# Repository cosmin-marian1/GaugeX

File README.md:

# GaugeX

A compact three-gauge automotive pod: three GC9A01 1.28" round SPI displays in
fused tubes, driven by an STM32G474, on one 3.3 V rail from switched ignition,
with a listen-only CAN interface.

| Part | State | Entry point |
|---|---|---|
| Enclosure (OpenSCAD) | done, STLs exported | [`3d-model/README.md`](3d-model/README.md) |
| Schematic | ERC 0 violations | [`pcb/DESIGN.md`](pcb/DESIGN.md) §5.3 |
| PCB | routed, planes filled, DRC 0 errors | [`pcb/README.md`](pcb/README.md) |
| BOM | generated from the schematic fields | [`pcb/BOM.md`](pcb/BOM.md) |
| Buck / front-end model | proxy model, timings checked | [`pcb/sim/README.md`](pcb/sim/README.md) |
| Firmware | not started | [`firmware/README.md`](firmware/README.md) |

Everything still open — including the items that block fabrication — is in
[`pcb/OPEN-ITEMS.md`](pcb/OPEN-ITEMS.md).

## Repository map

| Path | Contents |
|---|---|
| `3d-model/` | parametric OpenSCAD source, checkers, STLs, renders |
| `pcb/` | KiCad project (`pcb/GaugeX/`), design/BOM/status docs, simulation |
| `docs/datasheets/` | datasheet PDFs + index with verified page citations |
| `docs/archive/` | superseded documents, kept for traceability only |
| `firmware/` | STM32 firmware (placeholder) |

Each design value has one owner:

| Values | Owner |
|---|---|
| Electronics (power, buck, pins, interfaces, heights) | `pcb/DESIGN.md` |
| Board mechanics, stackup, routing, rules, DRC | `pcb/README.md` |
| Parts, MPN, LCSC | `pcb/BOM.md` |
| Enclosure dimensions and tolerances | `3d-model/README.md` |
| Open checks | `pcb/OPEN-ITEMS.md` |

## Build and verify

Enclosure (exports both STLs, checks the envelope, renders previews):

```bash
cd 3d-model/src && ./export_final.sh
```

Schematic and board checks:

```bash
kicad-cli sch erc pcb/GaugeX/GaugeX.kicad_sch
kicad-cli pcb drc pcb/GaugeX/GaugeX.kicad_pcb
```

BOM (exact field list and notes in `pcb/BOM.md`):

```bash
kicad-cli sch export bom \
  --fields "Reference,Value,Footprint,MPN,LCSC,QUANTITY,DNP" \
  --group-by "Value,Footprint,MPN,LCSC" \
  --output bom.csv pcb/GaugeX/GaugeX.kicad_sch
```

Buck / front-end model:

```bash
python3 pcb/sim/buck_sim.py
```

## Notes

- No 5 V rail; the whole board runs from one 3.3 V rail.
- CAN is listen-only by default (`S` pin on the transceiver).
- The three display modules are a separate purchase and are not in the BOM.
- Datasheet citations are collected in [`docs/datasheets/INDEX.md`](docs/datasheets/INDEX.md).

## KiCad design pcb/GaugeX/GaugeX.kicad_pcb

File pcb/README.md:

# PCB — board status

KiCad project: `pcb/GaugeX/GaugeX.kicad_pro`
Board: `pcb/GaugeX/GaugeX.kicad_pcb`
DRC/ERC data: `pcb/GaugeX/DRC_report.json`, `pcb/GaugeX/ERC_report.json`
Preview: `pcb/GaugeX/GaugeX_board_routed.png`

| Document | Contents |
|---|---|
| `pcb/DESIGN.md` | electrical design: power, buck, MCU pins, interfaces |
| `pcb/BOM.md` | parts list (generated from the schematic fields) |
| `pcb/OPEN-ITEMS.md` | open `[VERIFY]` / Rev-B / fab items |
| `pcb/sim/README.md` | buck/front-end model, its results and limits |
| `docs/datasheets/INDEX.md` | datasheet index with page citations |

## Project files

| Path | Contents |
|---|---|
| `GaugeX/` | KiCad project, schematic, board, local footprint library, previews |
| `GaugeX.pretty/` | project footprints (`GaugeX_SolderPad_1x04_P2.54mm`) |
| `sim/` | Python model of the buck and front end |

## Mechanical

| Item | Value |
|---|---|
| Outline | **50 × 40 mm**, r2.5 corners, 1.6 mm thick |
| Mounting holes | 4 × **Ø2.7 mm** (M2.5), Ø5.0 pad, pattern **44 × 34 mm** |
| Hole positions | (3,3), (47,3), (3,37), (47,37) |
| Footprints | **71** (67 parts + 4 mounting holes) |
| Power entry | **J1 = 4 SMD solder pads**, **1.6 × 2.6 mm**, 2.54 mm pitch, top edge |
| Protrusion below the board | **0 mm** — no THT component pads; only the 4 × Ø2.7 NPTH holes |

**Height rule:** front face (toward the displays) **≤ 5.0 mm**; back face
(toward the back plate) **≤ 3.0 mm** (3.4 mm cavity gap). Measured part heights
and verdicts are in `pcb/DESIGN.md` §7.

## Stackup

| Layer | Contents |
|---|---|
| F.Cu | signal + GND pour (all 67 parts) |
| In1.Cu | **solid GND plane**, no tracks |
| In2.Cu | **+3V3 pour** (priority 1) + GND fill |
| B.Cu | signal + GND pour |

All routing is on F.Cu/B.Cu. In1 is one continuous polygon; no slot, no split.
No SPI/CAN trace crosses a plane gap — the worst case is a trace edge grazing a
neighbouring via's antipad (0.12 mm of centreline inside a ~1 mm hole).

## Routing

| Item | Value |
|---|---|
| Tracks | **611** (F.Cu 381 / B.Cu 230) |
| Vias | **168** — 155 × 0.5/0.2, 11 × 0.6/0.3, 2 × 0.46/0.2 |
| Track widths | 0.20 mm signal, 0.60 mm power |
| Zones | F.Cu GND, B.Cu GND, In1 GND, In2 GND, In2 +3V3 — all filled |
| GND vias | 70 (22 per-pad fanout, 9 in U1 EP, 6 in U2 EP, 27 perimeter ring, island/plane ties, 1 at J1) |
| Signal tracks on In1/In2 | **0** |

## Design rules and fab tier

| Rule | Value |
|---|---|
| `Default` clearance / track / via | 0.12 mm / 0.20 mm / 0.5-0.2 |
| `Power` clearance / track / via | 0.15 mm / 0.60 mm / 0.6-0.3 |
| Min track width | 0.15 mm |
| Min via diameter / annular | 0.46 mm / 0.13 mm |
| Copper to edge | 0.30 mm |
| Hole clearance / hole-to-hole | 0.25 mm |

**JLCPCB standard 4-layer, no advanced option, no small-via surcharge.** The
0.2 mm hole is charged only below 0.45 mm diameter; 0.5 and 0.6 are free, and
the two 0.46 vias are 0.01 mm above the cutoff. Annular 0.15 mm (0.5/0.6 vias)
and 0.13 mm (0.46 vias) are at or above the 0.13 mm minimum.

## DRC

**0 errors, 0 unconnected, 4 warnings.** All four are
`lib_footprint_mismatch` on instances edited on purpose:

| Footprint | Deliberate difference |
|---|---|
| `C2`, `C5` | courtyard removed (pads sit flush with U2) |
| `U1` | 16 EP land pads given the GND net + F.Cu/F.Mask |
| `U2` | six 0.2 mm PTH pad-holes replaced by 0.5/0.2 vias |

ERC: **0 violations** (netlist table and result in `pcb/DESIGN.md` §5.3).

## Changes from the original layout

| Ref | Change | Reason |
|---|---|---|
| J1 | 1×04 THT header → 4 SMD pads, 1.6 × 2.6 mm | 8.65 mm above / 3.11 mm of pin below removed |
| D3 | (35.5, 7.5) → (29.0, 6.8) | ESD diode at the connector |
| C2 | (13.5, 11.0) → (6.05, 13.76) | input decoupling at U2 pins 1/2, planar |
| C5 | (22.0, 12.0) → (13.95, 13.90) | bootstrap loop at U2 pins 7/8 |
| U2 | thermal pads → 6 × 0.5/0.2 vias, tented | fab-friendly, no 0.2 mm PTH pads |

Deviations that stay (netclass clearance 0.12 mm, two 0.46 vias, removed C2/C5
courtyards) are listed with their justification in `pcb/OPEN-ITEMS.md`.

## Status

- Schematic: ERC clean, netlist verified.
- Board: routed, planes filled, DRC clean.
- Not done: Gerber/drill export, fab DFM sign-off. See `pcb/OPEN-ITEMS.md`.

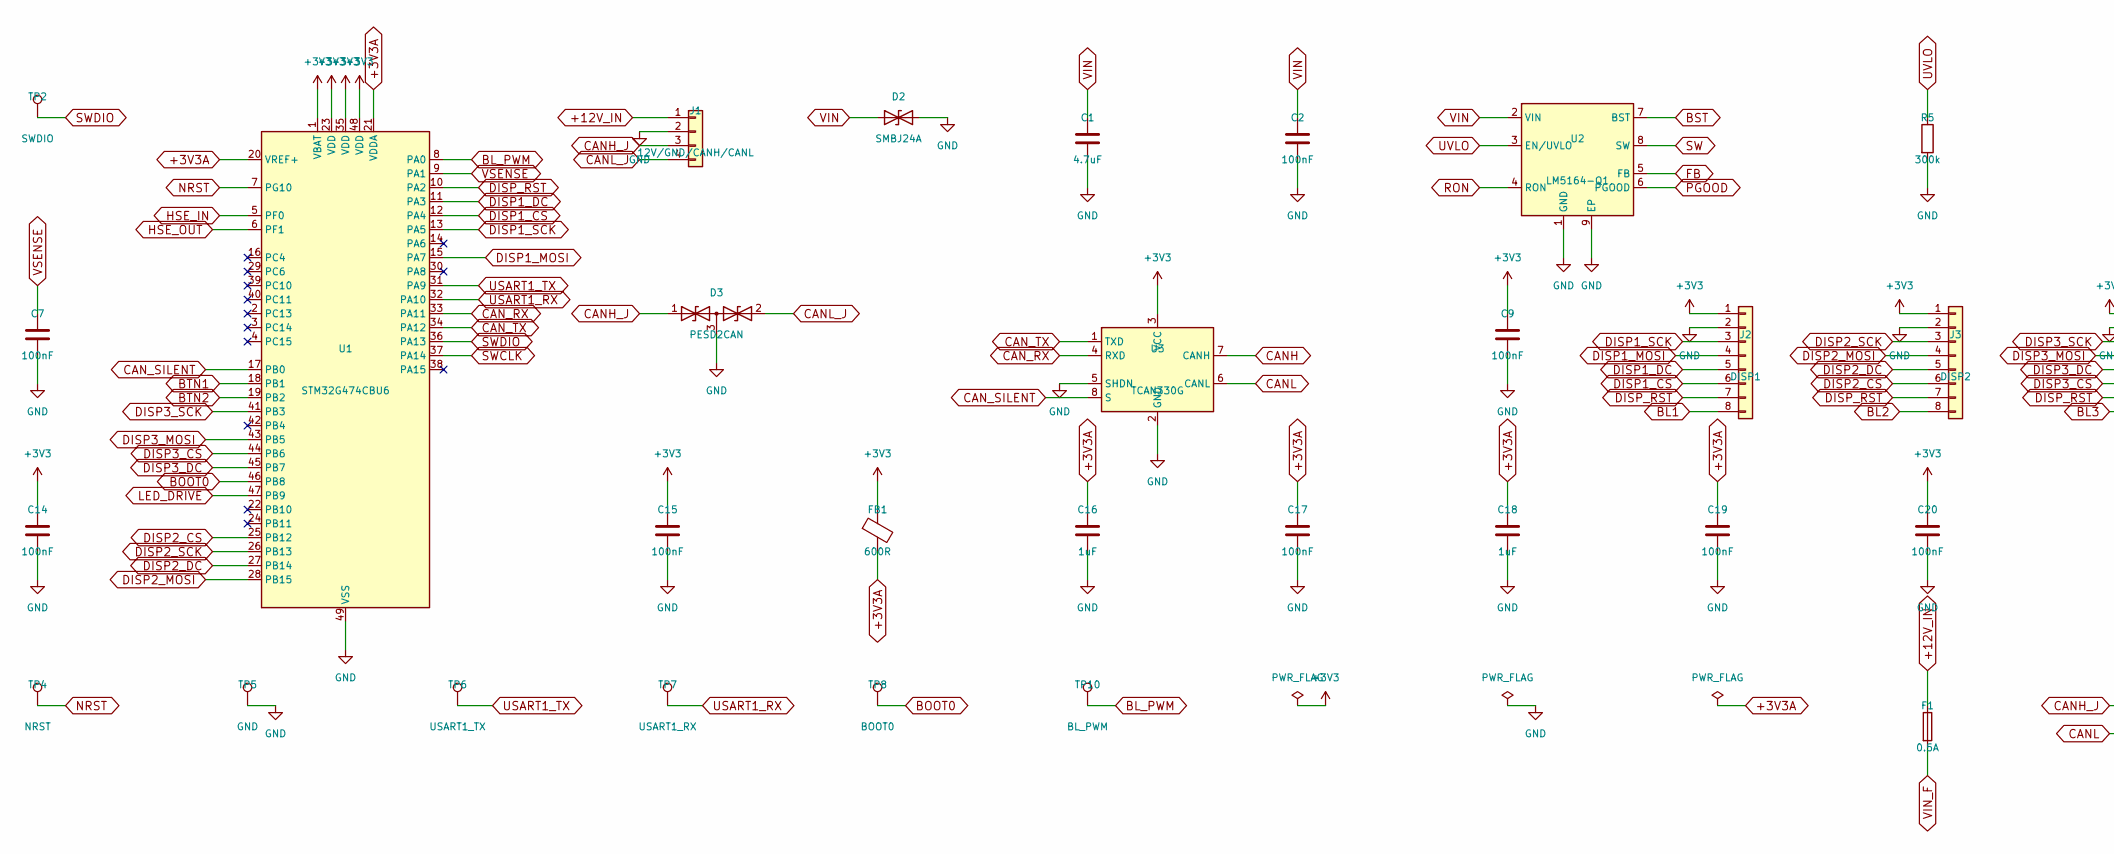
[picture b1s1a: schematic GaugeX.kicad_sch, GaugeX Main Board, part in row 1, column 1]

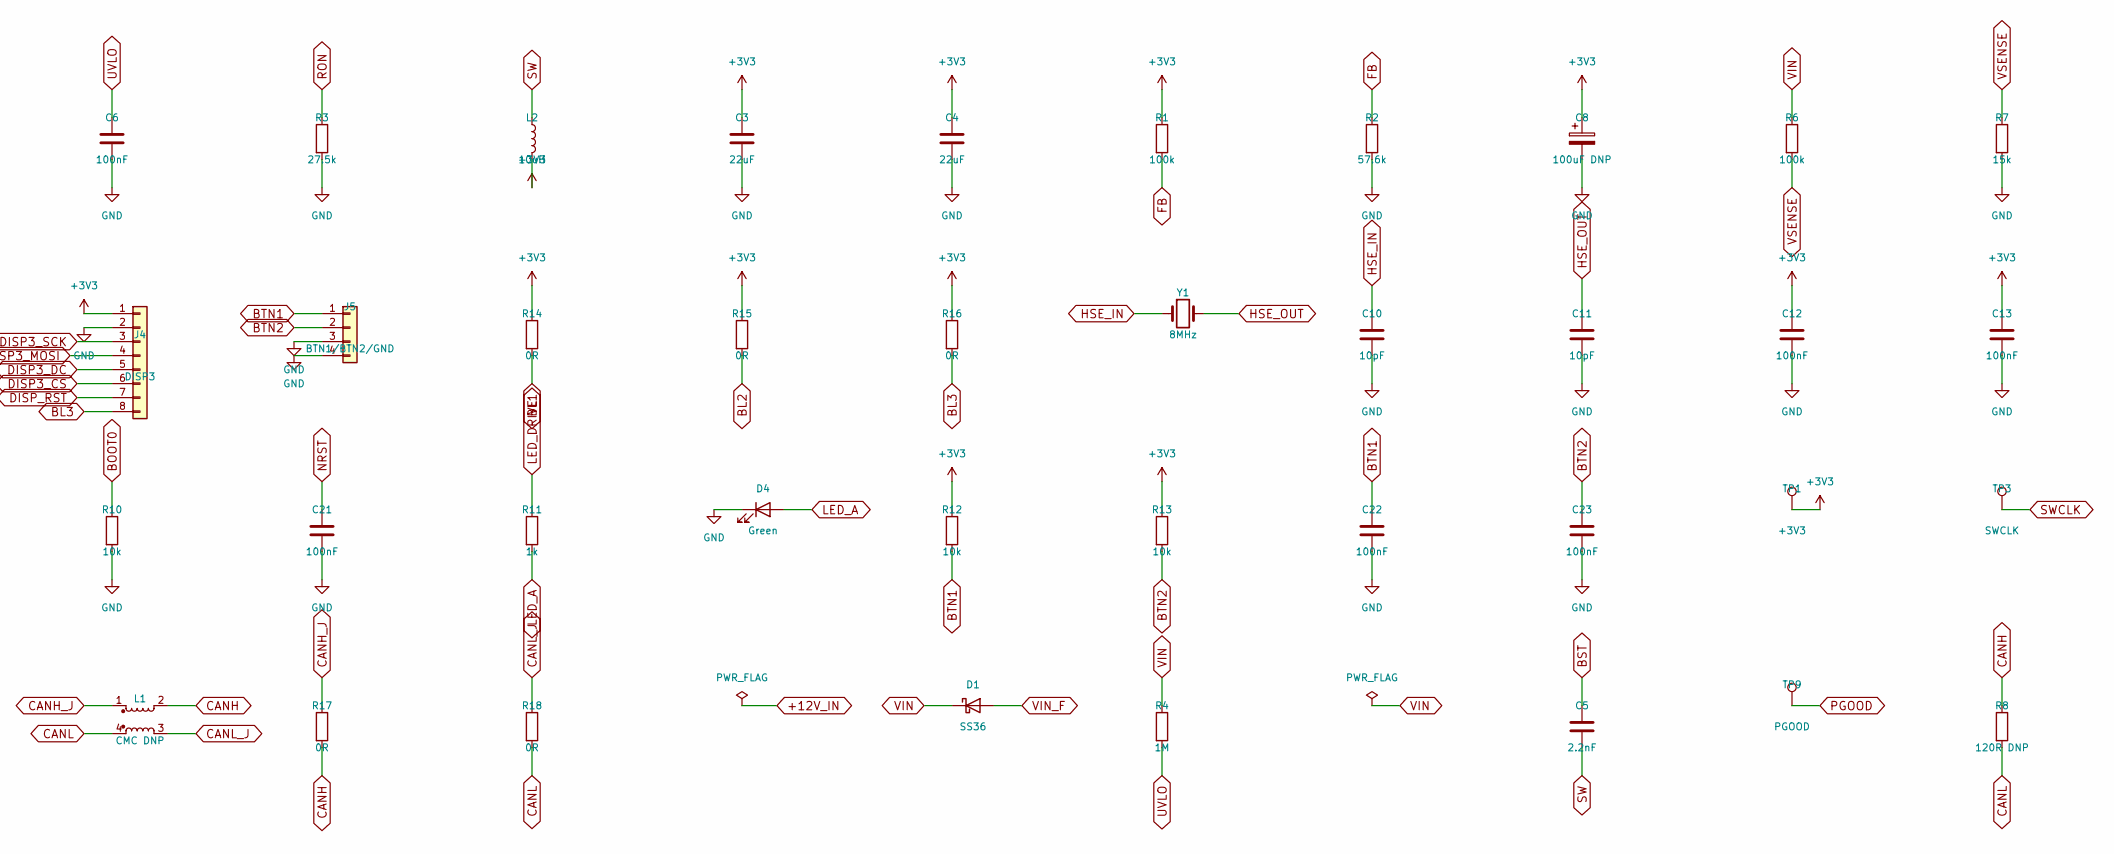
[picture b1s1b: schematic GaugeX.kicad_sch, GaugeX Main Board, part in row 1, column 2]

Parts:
C1: 4.7uF; C_0805_2012Metric
C2, C6, C7, C9, C12, C13, C14, C15, C17, C19, C20, C21, C22, C23: 100nF; C_0402_1005Metric
C3, C4: 22uF; C_0805_2012Metric
C5: 2.2nF; C_0402_1005Metric
C8: 100uF DNP; CP_Elec_6.3x4.5
C10, C11: 10pF; C_0402_1005Metric
C16, C18: 1uF; C_0402_1005Metric
D1: SS36; D_SMA
D2: SMBJ24A; D_SMB
D3: PESD2CAN; SOT-23
D4: Green; LED_0402_1005Metric
F1: 0.5A; Fuse_1206_3216Metric
FB1: 600R; L_0603_1608Metric
J1: 12V/GND/CANH/CANL; GaugeX_SolderPad_1x04_P2.54mm
J2: DISP1; JST_SH_SM08B-SRSS-TB_1x08-1MP_P1.00mm_Horizontal
J3: DISP2; JST_SH_SM08B-SRSS-TB_1x08-1MP_P1.00mm_Horizontal
J4: DISP3; JST_SH_SM08B-SRSS-TB_1x08-1MP_P1.00mm_Horizontal
J5: BTN1/BTN2/GND; JST_SH_SM04B-SRSS-TB_1x04-1MP_P1.00mm_Horizontal
L1: CMC DNP; L_CommonModeChoke_TDK_ACM2520-2P
L2: 10uH; L_Coilcraft_XAL5030-XXX
R1, R6: 100k; R_0402_1005Metric
R2: 57.6k; R_0402_1005Metric
R3: 27.5k; R_0402_1005Metric
R4: 1M; R_0402_1005Metric
R5: 300k; R_0402_1005Metric
R7: 15k; R_0402_1005Metric
R8: 120R DNP; R_0402_1005Metric
R10, R12, R13: 10k; R_0402_1005Metric
R11: 1k; R_0402_1005Metric
R14, R15, R16, R17, R18: 0R; R_0402_1005Metric
TP1: +3V3; TestPoint_Pad_D1.0mm
TP2: SWDIO; TestPoint_Pad_D1.0mm
TP3: SWCLK; TestPoint_Pad_D1.0mm
TP4: NRST; TestPoint_Pad_D1.0mm
TP5: GND; TestPoint_Pad_D1.0mm
TP6: USART1_TX; TestPoint_Pad_D1.0mm
TP7: USART1_RX; TestPoint_Pad_D1.0mm
TP8: BOOT0; TestPoint_Pad_D1.0mm
TP9: PGOOD; TestPoint_Pad_D1.0mm
TP10: BL_PWM; TestPoint_Pad_D1.0mm
U1: STM32G474CBU6; QFN-48-1EP_7x7mm_P0.5mm_EP5.6x5.6mm
U2: LM5164-Q1; HSOP-8-1EP_3.9x4.9mm_P1.27mm_EP2.41x3.1mm_ThermalVias
U3: TCAN330G; SOIC-8_3.9x4.9mm_P1.27mm
Y1: 8MHz; Crystal_SMD_3215-2Pin_3.2x1.5mm

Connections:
+3V3: C3.1, C4.1, C8.1, C9.1, C12.1, C13.1, C14.1, C15.1, C20.1, FB1.1, J2.1, J3.1, J4.1, L2.2, R1.1, R12.1, R13.1, R14.1, R15.1, R16.1, TP1.1, U1.1 (VBAT), U1.23 (VDD), U1.35 (VDD), U1.48 (VDD), U3.3 (VCC)
+3V3A: C16.1, C17.1, C18.1, C19.1, FB1.2, U1.20 (VREF+), U1.21 (VDDA)
+12V_IN: F1.1, J1.1
BL1: J2.8, R14.2
BL2: J3.8, R15.2
BL3: J4.8, R16.2
BL_PWM: TP10.1, U1.8 (PA0)
BOOT0: R10.1, TP8.1, U1.46 (PB8)
BST: C5.1, U2.7 (BST)
BTN1: C22.1, J5.1, R12.2, U1.18 (PB1)
BTN2: C23.1, J5.2, R13.2, U1.19 (PB2)
CANH: L1.2, R8.1, R17.2, U3.7 (CANH)
CANH_J: D3.1 (A1), J1.3, L1.1, R17.1
CANL: L1.4, R8.2, R18.2, U3.6 (CANL)
CANL_J: D3.2 (A2), J1.4, L1.3, R18.1
CAN_RX: U1.33 (PA11), U3.4 (RXD)
CAN_SILENT: U1.17 (PB0), U3.8 (S)
CAN_TX: U1.34 (PA12), U3.1 (TXD)
DISP1_CS: J2.6, U1.12 (PA4)
DISP1_DC: J2.5, U1.11 (PA3)
DISP1_MOSI: J2.4, U1.15 (PA7)
DISP1_SCK: J2.3, U1.13 (PA5)
DISP2_CS: J3.6, U1.25 (PB12)
DISP2_DC: J3.5, U1.27 (PB14)
DISP2_MOSI: J3.4, U1.28 (PB15)
DISP2_SCK: J3.3, U1.26 (PB13)
DISP3_CS: J4.6, U1.44 (PB6)
DISP3_DC: J4.5, U1.45 (PB7)
DISP3_MOSI: J4.4, U1.43 (PB5)
DISP3_SCK: J4.3, U1.41 (PB3)
DISP_RST: J2.7, J3.7, J4.7, U1.10 (PA2)
FB: R1.2, R2.1, U2.5 (FB)
GND: C1.2, C2.2, C3.2, C4.2, C6.2, C7.2, C8.2, C9.2, C10.2, C11.2, C12.2, C13.2, C14.2, C15.2, C16.2, C17.2, C18.2, C19.2, C20.2, C21.2, C22.2, C23.2, D2.2 (A2), D3.3 (common), D4.1 (K), J1.2, J2.2, J3.2, J4.2, J5.3, J5.4, R2.2, R3.2, R5.2, R7.2, R10.2, TP5.1, U1.49 (VSS), U2.1 (GND), U2.9 (EP), U3.2 (GND), U3.5 (SHDN)
HSE_IN: C10.1, U1.5 (PF0), Y1.1
HSE_OUT: C11.1, U1.6 (PF1), Y1.2
LED_A: D4.2 (A), R11.2
LED_DRIVE: R11.1, U1.47 (PB9)
NRST: C21.1, TP4.1, U1.7 (PG10)
PGOOD: TP9.1, U2.6 (PGOOD)
RON: R3.1, U2.4 (RON)
SW: C5.2, L2.1, U2.8 (SW)
SWCLK: TP3.1, U1.37 (PA14)
SWDIO: TP2.1, U1.36 (PA13)
USART1_RX: TP7.1, U1.32 (PA10)
USART1_TX: TP6.1, U1.31 (PA9)
UVLO: C6.1, R4.2, R5.1, U2.3 (EN/UVLO)
VIN: C1.1, C2.1, D1.1 (K), D2.1 (A1), R4.1, R6.1, U2.2 (VIN)
VIN_F: D1.2 (A), F1.2
VSENSE: C7.1, R6.2, R7.1, U1.9 (PA1)

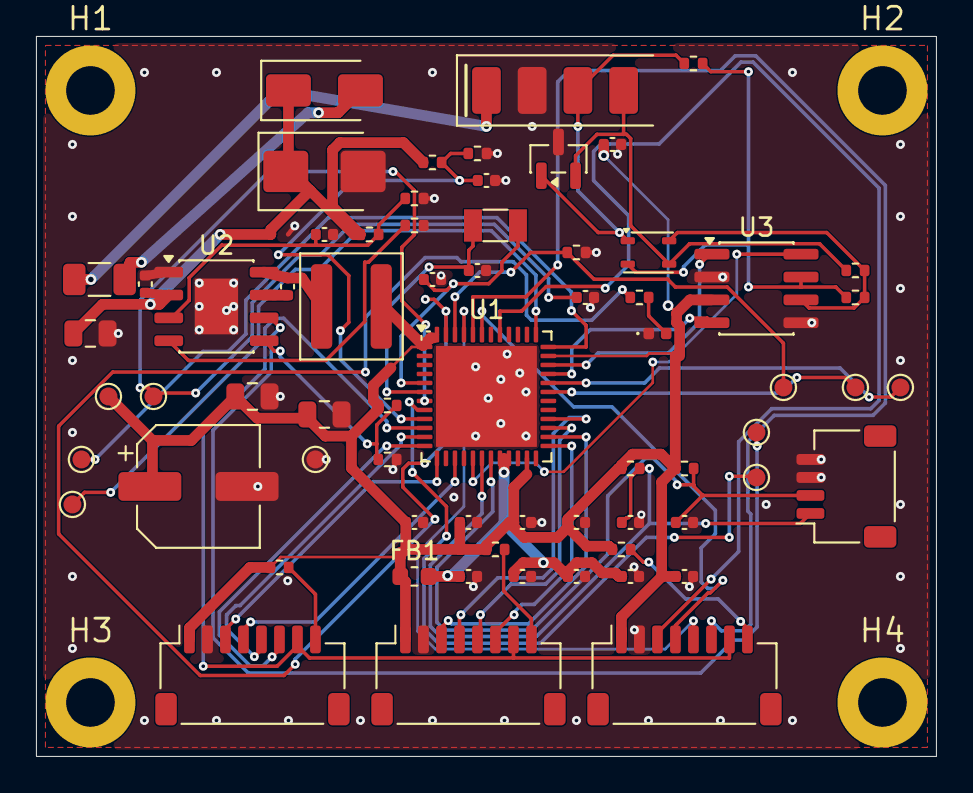
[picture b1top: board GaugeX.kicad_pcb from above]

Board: 4 copper layers, 50.0 x 40.0 mm, 71 parts (0 on the bottom side), 49 nets.

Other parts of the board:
H1, H2, H3, H4: MountingHole_5.00mm
